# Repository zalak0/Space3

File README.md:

# Space3
Satellite code simulation and STM32 implementation of that code

## Structure

- **Simulation** folder includes code that simulates given code that is NOT in STM32.
- **STM32 Implementation** folder includes code that will be used for the STM32/in the satellite
> Organise each sub-folder into subsystem based folders rather than simulation-specific folders for modularity.

## STM32 tutorials
The following tutorials might help for STM32 coding. It might be a good idea to spend some time to actually learnt his since **STM32 is a complicated yet powerful platform**:

### STM32 basics

### Learn how to use HAL and functionality

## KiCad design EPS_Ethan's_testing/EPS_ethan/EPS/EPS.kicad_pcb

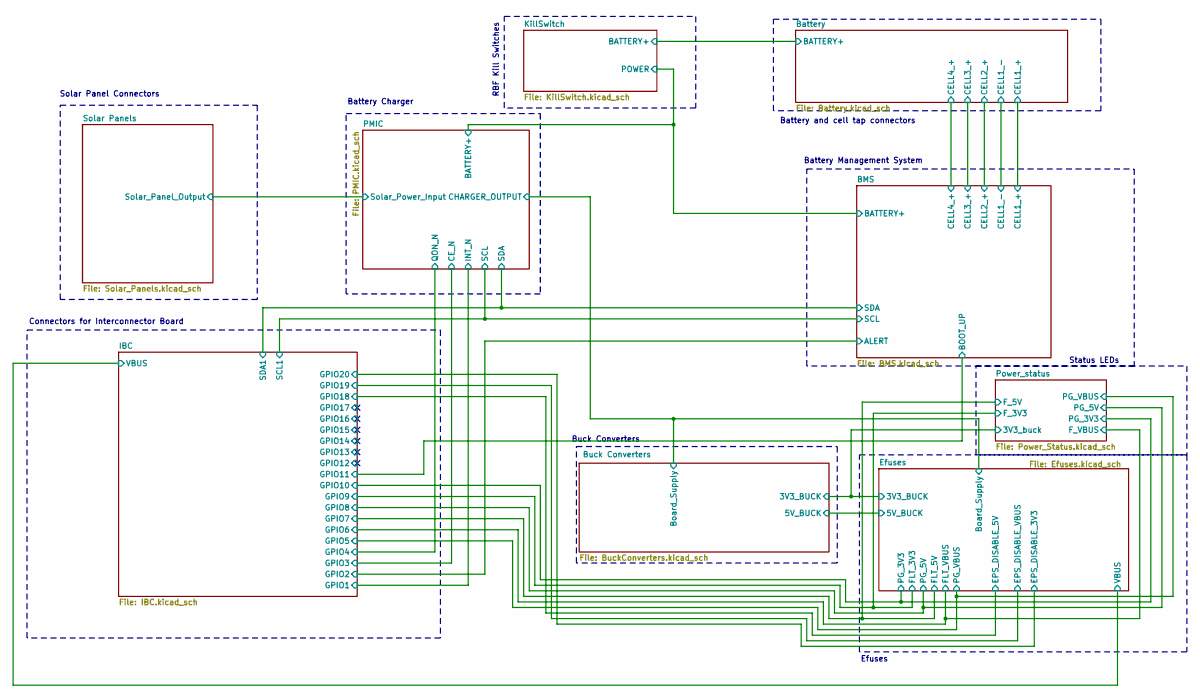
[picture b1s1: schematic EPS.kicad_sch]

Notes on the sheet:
Buck Converters
Battery Management System
Efuses
Battery and cell tap connectors
Status LEDs
Battery Charger
Connectors for Interconnector Board
Solar Panel Connectors
RBF Kill Switches

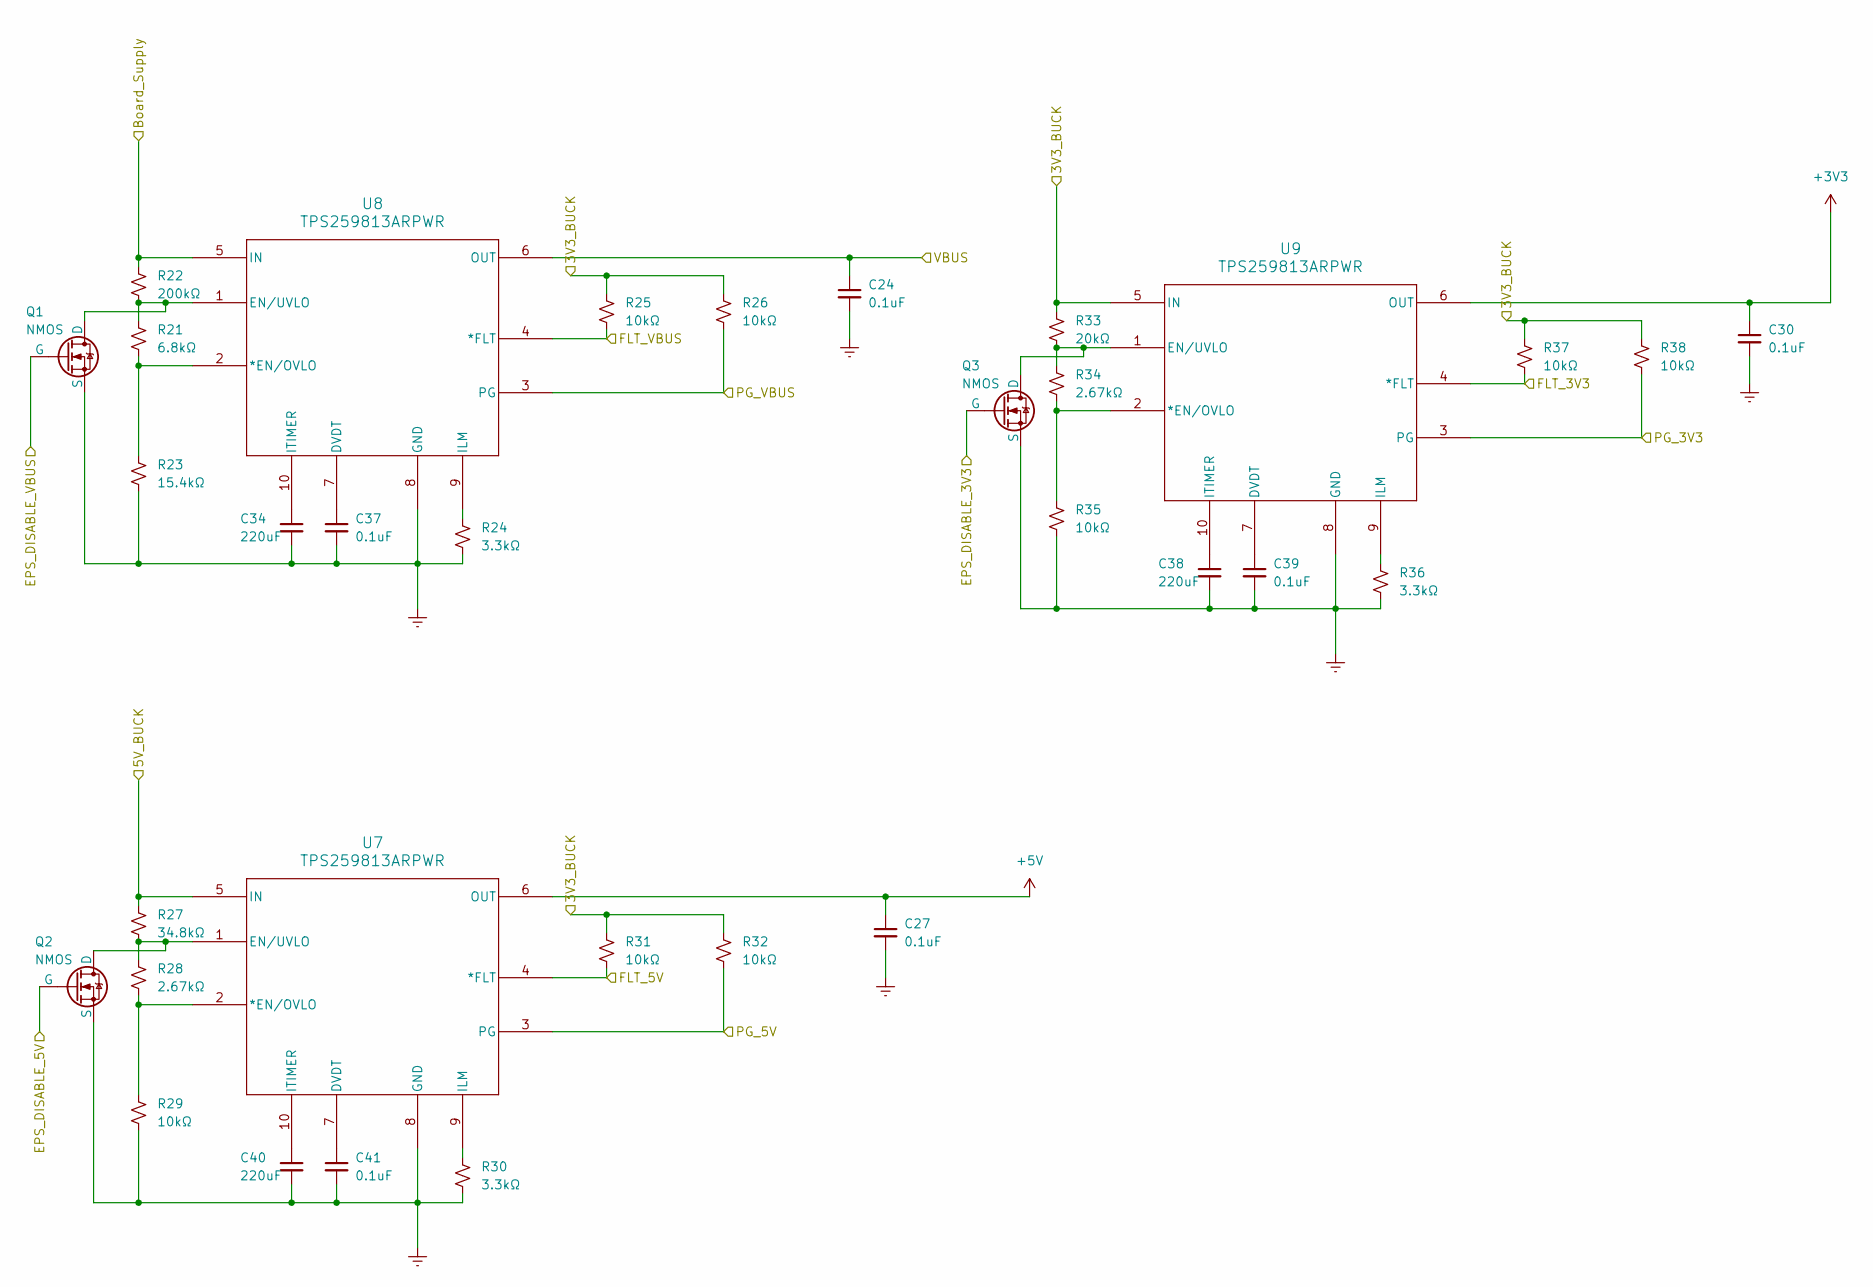
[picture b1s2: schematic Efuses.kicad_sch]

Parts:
C24, C27, C30, C37, C39, C41: 0.1uF; C_0402_1005Metric_Pad0.74x0.62mm_HandSolder; LCSC C1525
C34, C38, C40: 220uF; C_0402_1005Metric_Pad0.74x0.62mm_HandSolder; LCSC C16651
Q1, Q2, Q3: NMOS; SOT95P240X111-3N; LCSC C8545
R21: 6.8kΩ; R_0201_0603Metric; LCSC C144024
R22: 200kΩ; R_0201_0603Metric; LCSC C102705
R23: 15.4kΩ; R_0201_0603Metric; LCSC C166345
R24, R30, R36: 3.3kΩ; R_0201_0603Metric; LCSC C170206
R25, R26, R29, R31, R32, R35, R37, R38: 10kΩ; R_0201_0603Metric; LCSC C100126
R27: 34.8kΩ; R_0201_0603Metric; LCSC C180320
R28, R34: 2.67kΩ; R_0201_0603Metric; LCSC C158664
R33: 20kΩ; R_0201_0603Metric; LCSC C100134
U7, U8, U9: TPS259813ARPWR; VQFN10_RPW_TEX; LCSC C22427533

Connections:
+3V3: C30.1, U9.6 (OUT); also elsewhere on the board
+5V: C27.1, U7.6 (OUT); also elsewhere on the board
/Buck Converters/3V3_BUCK: R25.1, R26.1, R31.1, R32.1, R33.1, R37.1, R38.1, U9.5 (IN); also elsewhere on the board
/Buck Converters/5V_BUCK: R27.1, U7.5 (IN); also elsewhere on the board
/Buck Converters/Board_Supply: R22.1, U8.5 (IN); also elsewhere on the board
/Efuses/EPS_DISABLE_3V3: Q3.2 (G); also elsewhere on the board
/Efuses/EPS_DISABLE_5V: Q2.2 (G); also elsewhere on the board
/Efuses/EPS_DISABLE_VBUS: Q1.2 (G); also elsewhere on the board
/Efuses/FLT_3V3: R37.2, U9.4 (*FLT); also elsewhere on the board
/Efuses/FLT_5V: R31.2, U7.4 (*FLT); also elsewhere on the board
/Efuses/FLT_VBUS: R25.2, U8.4 (*FLT); also elsewhere on the board
/Efuses/PG_3V3: R38.2, U9.3 (PG); also elsewhere on the board
/Efuses/PG_5V: R32.2, U7.3 (PG); also elsewhere on the board
/Efuses/PG_VBUS: R26.2, U8.3 (PG); also elsewhere on the board
/Efuses/VBUS: C24.1, U8.6 (OUT); also elsewhere on the board
Earth: C24.2, C27.2, C30.2, C34.2, C37.2, C38.2, C39.2, C40.2, C41.2, Q1.3 (S), Q2.3 (S), Q3.3 (S), R23.2, R24.2, R29.2, R30.2, R35.2, R36.2, U7.8 (GND), U8.8 (GND), U9.8 (GND); also elsewhere on the board
unnamed: Q1.1 (D), R21.1, R22.2, U8.1 (EN/UVLO)
unnamed: Q2.1 (D), R27.2, R28.1, U7.1 (EN/UVLO)
unnamed: Q3.1 (D), R33.2, R34.1, U9.1 (EN/UVLO)
unnamed: R28.2, R29.1, U7.2 (*EN/OVLO)
unnamed: C41.1, U7.7 (DVDT)
unnamed: R30.1, U7.9 (ILM)
unnamed: C40.1, U7.10 (ITIMER)
unnamed: R21.2, R23.1, U8.2 (*EN/OVLO)
unnamed: C37.1, U8.7 (DVDT)
unnamed: R24.1, U8.9 (ILM)
unnamed: C34.1, U8.10 (ITIMER)
unnamed: R34.2, R35.1, U9.2 (*EN/OVLO)
unnamed: C39.1, U9.7 (DVDT)
unnamed: R36.1, U9.9 (ILM)
unnamed: C38.1, U9.10 (ITIMER)

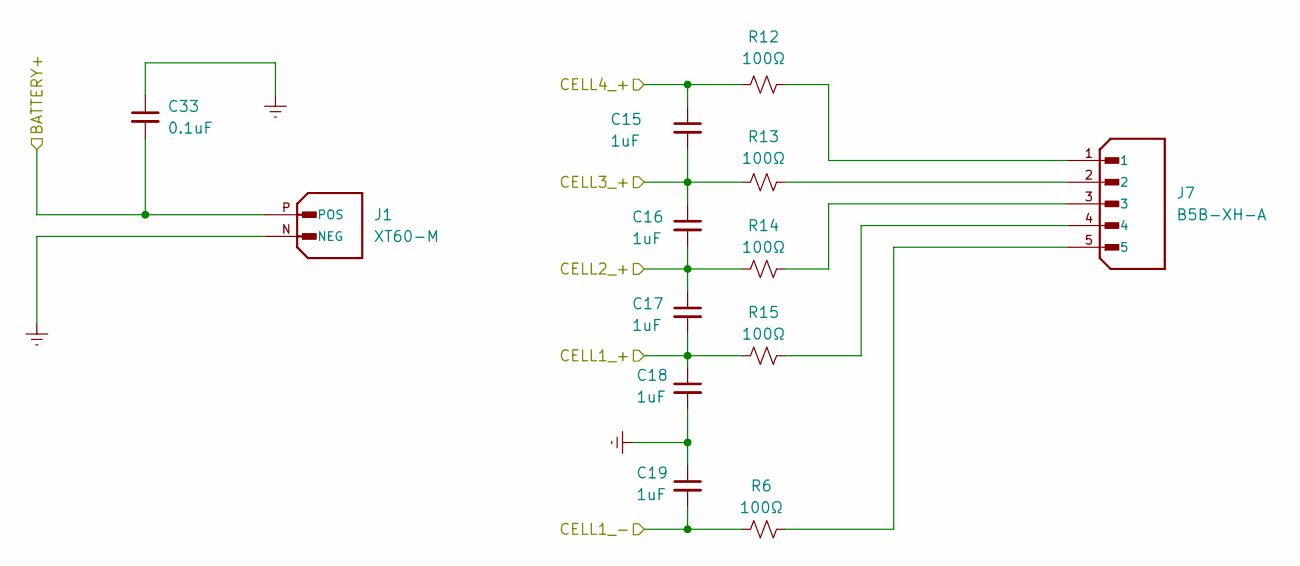
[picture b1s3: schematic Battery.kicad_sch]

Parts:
C15, C16, C17, C18, C19: 1uF; C_0402_1005Metric_Pad0.74x0.62mm_HandSolder; LCSC C14445
C33: 0.1uF; C_0402_1005Metric_Pad0.74x0.62mm_HandSolder; LCSC C1525
J1: XT60-M; AMASS_XT60-M; PARTREV V1.2; LCSC C98733
J7: B5B-XH-A; JST_B5B-XH-A; PARTREV 7/4/21; LCSC C157991
R6, R12, R13, R14, R15: 100Ω; R_0201_0603Metric; LCSC C77623

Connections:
/BMS/CELL1_+: C17.2, C18.1, R15.1; also elsewhere on the board
/BMS/CELL1_-: C19.2, R6.1; also elsewhere on the board
/BMS/CELL2_+: C16.2, C17.1, R14.1; also elsewhere on the board
/BMS/CELL3_+: C15.2, C16.1, R13.1; also elsewhere on the board
/BMS/CELL4_+: C15.1, R12.1; also elsewhere on the board
/Battery/BATTERY+: C33.2, J1.P (POS); also elsewhere on the board
Earth: C18.2, C19.1, C33.1, J1.N (NEG); also elsewhere on the board
unnamed: J7.1, R12.2
unnamed: J7.2, R13.2
unnamed: J7.3, R14.2
unnamed: J7.4, R15.2
unnamed: J7.5, R6.2

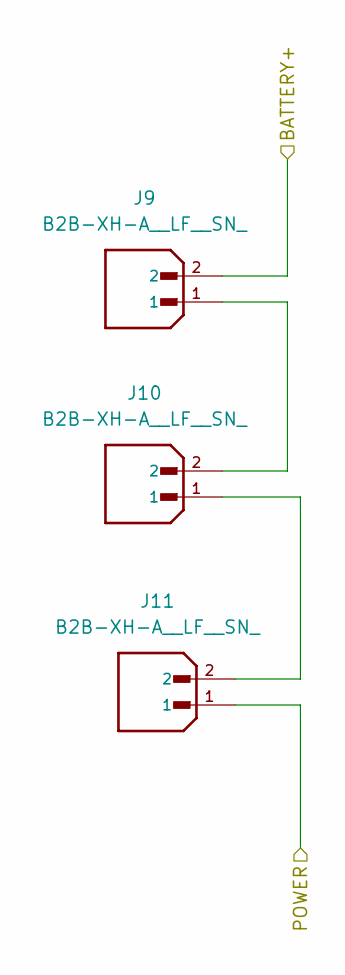
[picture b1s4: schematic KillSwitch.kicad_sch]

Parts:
J9, J10, J11: B2B-XH-A__LF__SN_; JST_B2B-XH-A__LF__SN_; PARTREV N/A; LCSC C158012

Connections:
/BMS/BATTERY+: J11.1; also elsewhere on the board
/Battery/BATTERY+: J9.2; also elsewhere on the board
unnamed: J10.1, J11.2
unnamed: J9.1, J10.2

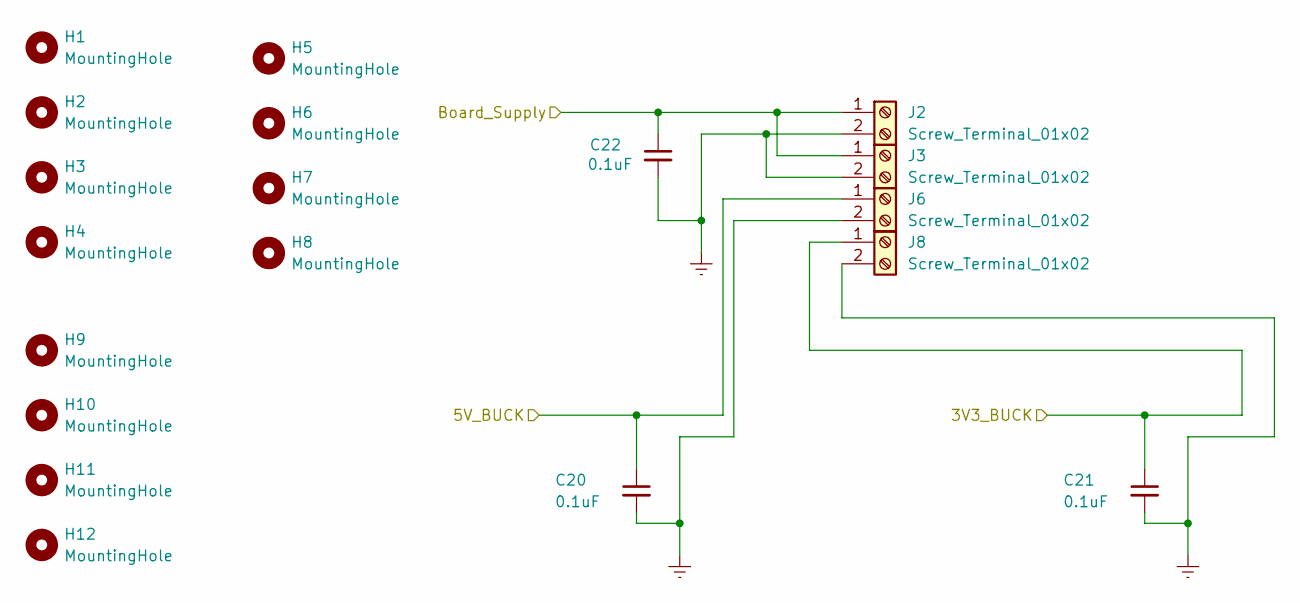
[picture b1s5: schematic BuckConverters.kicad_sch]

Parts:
C20, C21, C22: 0.1uF; C_0402_1005Metric_Pad0.74x0.62mm_HandSolder; LCSC C1525
H1, H2, H3, H4, H5, H6, H7, H8, H9, H10, H11, H12: MountingHole; MountingHole_3.2mm_M3
J2, J3, J6, J8: Screw_Terminal_01x02; HANDSON_KF301-2P; LCSC C474881

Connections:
/Buck Converters/3V3_BUCK: C21.1, J8.1; also elsewhere on the board
/Buck Converters/5V_BUCK: C20.1, J6.1; also elsewhere on the board
/Buck Converters/Board_Supply: C22.1, J2.1, J3.1; also elsewhere on the board
Earth: C20.2, C21.2, C22.2, J2.2, J3.2, J6.2, J8.2; also elsewhere on the board

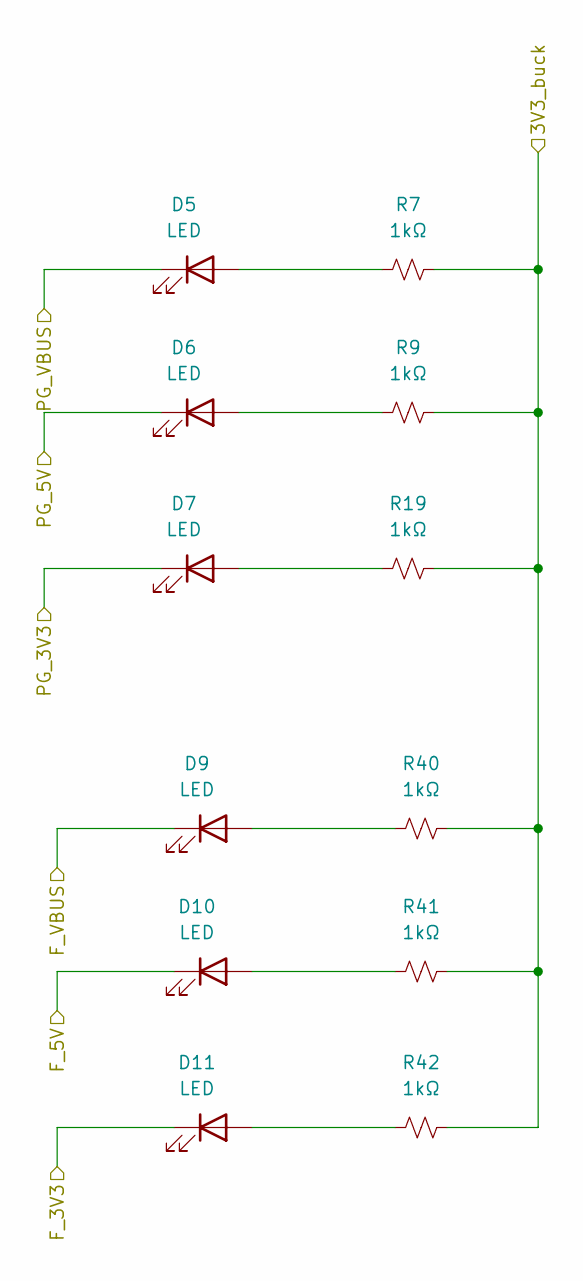
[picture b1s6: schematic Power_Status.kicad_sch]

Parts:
D5, D6, D7: LED; LED_0603_1608Metric; LCSC C510029
D9, D10, D11: LED; LED_0603_1608Metric; LCSC C79636
R7, R9, R19, R40, R41, R42: 1kΩ; R_0201_0603Metric; LCSC C100125

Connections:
/Buck Converters/3V3_BUCK: R7.2, R9.2, R19.2, R40.2, R41.2, R42.2; also elsewhere on the board
/Efuses/FLT_3V3: D11.1 (K); also elsewhere on the board
/Efuses/FLT_5V: D10.1 (K); also elsewhere on the board
/Efuses/FLT_VBUS: D9.1 (K); also elsewhere on the board
/Efuses/PG_3V3: D7.1 (K); also elsewhere on the board
/Efuses/PG_5V: D6.1 (K); also elsewhere on the board
/Efuses/PG_VBUS: D5.1 (K); also elsewhere on the board
unnamed: D5.2 (A), R7.1
unnamed: D6.2 (A), R9.1
unnamed: D7.2 (A), R19.1
unnamed: D9.2 (A), R40.1
unnamed: D10.2 (A), R41.1
unnamed: D11.2 (A), R42.1

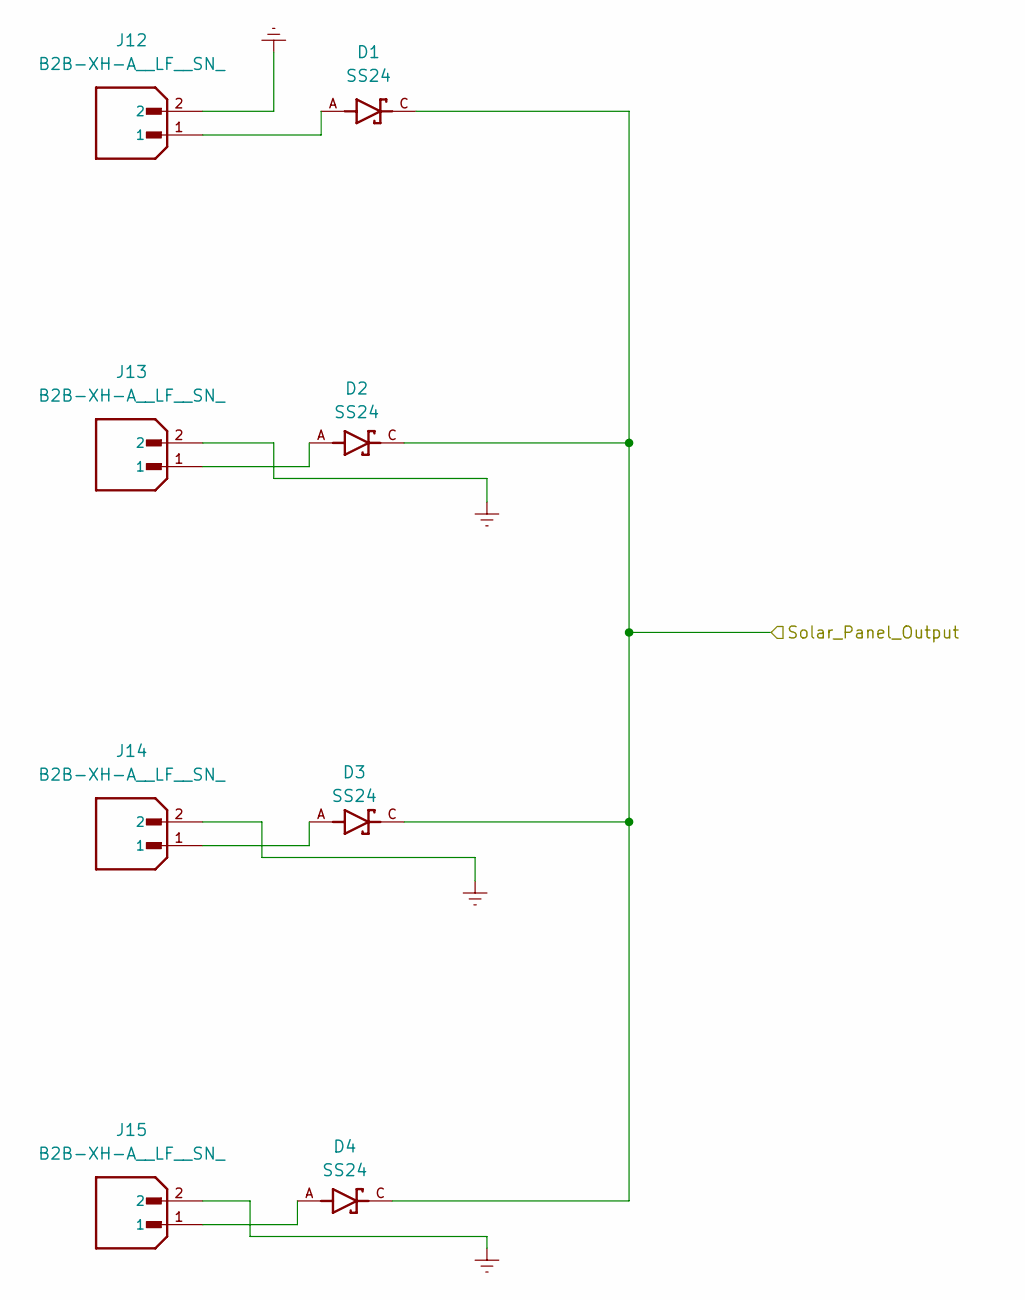
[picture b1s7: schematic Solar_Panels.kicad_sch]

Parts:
D1, D2, D3, D4: SS24; DIOM5336X265N; PARTREV 1.1.2; LCSC C50645
J12, J13, J14, J15: B2B-XH-A__LF__SN_; JST_B2B-XH-A__LF__SN_; PARTREV N/A; LCSC C158012

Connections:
/PMIC/Solar_Power_Input: D1.C, D2.C, D3.C, D4.C; also elsewhere on the board
Earth: J12.2, J13.2, J14.2, J15.2; also elsewhere on the board
unnamed: D1.A, J12.1
unnamed: D2.A, J13.1
unnamed: D3.A, J14.1
unnamed: D4.A, J15.1

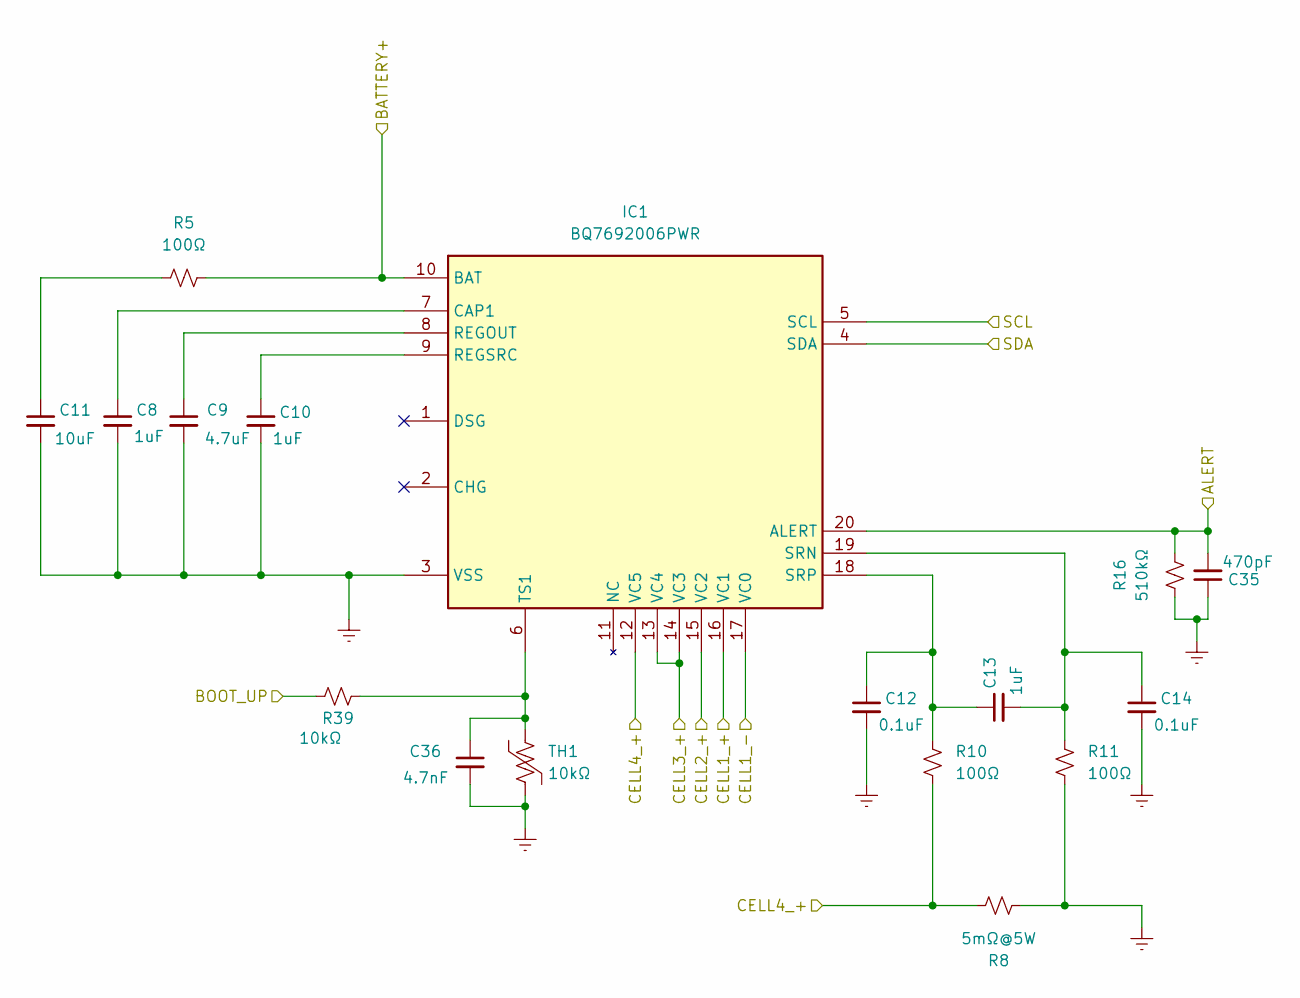
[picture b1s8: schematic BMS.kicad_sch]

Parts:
C8, C10, C13: 1uF; C_0402_1005Metric_Pad0.74x0.62mm_HandSolder; LCSC C83063
C9: 4.7uF; C_0402_1005Metric_Pad0.74x0.62mm_HandSolder; LCSC C23687
C11: 10uF; C_0402_1005Metric_Pad0.74x0.62mm_HandSolder; LCSC C77000
C12, C14: 0.1uF; C_0402_1005Metric_Pad0.74x0.62mm_HandSolder; LCSC C1525
C35: 470pF; C_0402_1005Metric_Pad0.74x0.62mm_HandSolder; LCSC C1537
C36: 4.7nF; C_0402_1005Metric_Pad0.74x0.62mm_HandSolder; LCSC C1538
IC1: BQ7692006PWR; SOP65P640X120-20N; Mouser Part Number 595-BQ7692006PWR
R5, R10, R11: 100Ω; R_0201_0603Metric; LCSC C77623
R8: 5mΩ@5W; RESC6432X90N; LCSC C840612
R16: 510kΩ; R_0201_0603Metric; LCSC C295805
R39: 10kΩ; R_0201_0603Metric; LCSC C100126
TH1: 10kΩ; R_0201_0603Metric; LCSC C92037

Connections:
/BMS/ALERT: C35.2, IC1.20 (ALERT), R16.2; also elsewhere on the board
/BMS/BATTERY+: IC1.10 (BAT), R5.1; also elsewhere on the board
/BMS/BOOT_UP: R39.1; also elsewhere on the board
/BMS/CELL1_+: IC1.16 (VC1); also elsewhere on the board
/BMS/CELL1_-: IC1.17 (VC0); also elsewhere on the board
/BMS/CELL2_+: IC1.15 (VC2); also elsewhere on the board
/BMS/CELL3_+: IC1.13 (VC4), IC1.14 (VC3); also elsewhere on the board
/BMS/CELL4_+: IC1.12 (VC5), R8.1, R10.2; also elsewhere on the board
/BMS/SCL: IC1.5 (SCL); also elsewhere on the board
/BMS/SDA: IC1.4 (SDA); also elsewhere on the board
Earth: C8.2, C9.2, C10.2, C11.2, C12.2, C14.2, C35.1, C36.2, IC1.3 (VSS), R8.2, R11.2, R16.1, TH1.2; also elsewhere on the board
unnamed: C11.1, R5.2
unnamed: C8.1, IC1.7 (CAP1)
unnamed: C9.1, IC1.8 (REGOUT)
unnamed: C10.1, IC1.9 (REGSRC)
unnamed: C13.2, C14.1, IC1.19 (SRN), R11.1
unnamed: C12.1, C13.1, IC1.18 (SRP), R10.1
unnamed: C36.1, IC1.6 (TS1), R39.2, TH1.1

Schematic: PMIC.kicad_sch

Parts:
C1, C25: 0.1uF; C_0402_1005Metric_Pad0.74x0.62mm_HandSolder; LCSC C1525
C2, C3: 47nF; C_0402_1005Metric_Pad0.74x0.62mm_HandSolder; LCSC C77012
C4: 4.7uF; C_0402_1005Metric_Pad0.74x0.62mm_HandSolder; LCSC C23687
C5: 0.1uF; C_0402_1005Metric_Pad0.74x0.62mm_HandSolder; LCSC C77000
C6, C7, C23, C26, C28, C29, C31, C32: 10uF; C_0402_1005Metric_Pad0.74x0.62mm_HandSolder; LCSC C77000
D8: LED; LED_0603_1608Metric; LCSC C510029
L1: 1.0uH; IND_ETQP3M1R0KVP; LCSC C409620
R1: 27kΩ; R_0201_0603Metric; LCSC C273283
R2: 13kΩ; R_0201_0603Metric; LCSC C158813
R3: 100Ω; R_0201_0603Metric; LCSC C77623
R4: 30kΩ; R_0201_0603Metric; LCSC C138105
R17, R20, R43: 10kΩ; R_0201_0603Metric; LCSC C100126
R18: 6.04kΩ; R_0201_0603Metric; LCSC C158428
TH2: 10KΩ; R_0201_0603Metric; LCSC C92037
U5: BQ25798RQMR; RQM0029A-MFG_fixed; LCSC C2876593

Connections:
+3V3: R17.1, R43.1; also elsewhere on the board
/BMS/BATTERY+: R3.2, U5.22 (BAT), U5.23 (BAT), U5.24 (SDRV); also elsewhere on the board
/BMS/SCL: U5.14 (SCL); also elsewhere on the board
/BMS/SDA: U5.15 (SDA); also elsewhere on the board
/Buck Converters/Board_Supply: C25.1, C26.1, C28.1, C29.1, C31.1, C32.1, U5.25 (SYS); also elsewhere on the board
/IBC/GPIO1: R43.2, U5.21 (INT_N); also elsewhere on the board
/IBC/GPIO3: R17.2, U5.13 (CE_N); also elsewhere on the board
/IBC/GPIO4: U5.12 (QON_N); also elsewhere on the board
/PMIC/REGEN: C4.1, R2.1, R18.1, U5.5 (REGN)
/PMIC/Solar_Power_Input: C1.1, U5.2 (VBUS), U5.3 (VBUS); also elsewhere on the board
Earth: C1.2, C4.2, C5.2, C6.2, C7.2, C23.2, C25.2, C26.2, C28.2, C29.2, C31.2, C32.2, R1.2, R4.1, R20.2, TH2.2, U5.10 (ACDRV2), U5.11 (ACDRV1), U5.27 (GND); also elsewhere on the board
unnamed: D8.2 (A), R18.2
unnamed: D8.1 (K), U5.1 (STAT)
unnamed: R3.1, U5.18 (BATP)
unnamed: C2.1, U5.4 (BTST1)
unnamed: C3.2, U5.19 (BTST2)
unnamed: R2.2, R20.1, U5.17 (ILIM_HIZ)
unnamed: C5.1, C6.1, C7.1, C23.1, U5.29 (PMID)
unnamed: R1.1, U5.20 (PROG)
unnamed: C2.2, L1.2, U5.28 (SW1)
unnamed: C3.1, L1.1, U5.26 (SW2)
unnamed: R4.2, TH2.1, U5.16 (TS)
unnamed: U5.8 (VAC2), U5.9 (VAC1)

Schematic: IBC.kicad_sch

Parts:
J4, J5: M20-6112045; HARWIN_M20-6112045; PARTREV 13

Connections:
+3V3: J4.3; also elsewhere on the board
+5V: J4.2; also elsewhere on the board
/BMS/ALERT: J4.9; also elsewhere on the board
/BMS/BOOT_UP: J4.27; also elsewhere on the board
/BMS/SCL: J4.6; also elsewhere on the board
/BMS/SDA: J4.8; also elsewhere on the board
/Efuses/EPS_DISABLE_3V3: J4.10; also elsewhere on the board
/Efuses/EPS_DISABLE_5V: J4.14; also elsewhere on the board
/Efuses/EPS_DISABLE_VBUS: J4.12; also elsewhere on the board
/Efuses/FLT_3V3: J4.23; also elsewhere on the board
/Efuses/FLT_5V: J4.19; also elsewhere on the board
/Efuses/FLT_VBUS: J4.17; also elsewhere on the board
/Efuses/PG_3V3: J4.25; also elsewhere on the board
/Efuses/PG_5V: J4.21; also elsewhere on the board
/Efuses/PG_VBUS: J4.15; also elsewhere on the board
/Efuses/VBUS: J4.1; also elsewhere on the board
/IBC/GPIO1: J4.7; also elsewhere on the board
/IBC/GPIO3: J4.11; also elsewhere on the board
/IBC/GPIO4: J4.13; also elsewhere on the board
/IBC/GPIO12: J4.29
/IBC/GPIO13: J4.31
/IBC/GPIO14: J4.33
/IBC/GPIO15: J4.35
/IBC/GPIO16: J4.37
/IBC/GPIO17: J4.39
Earth: J4.4, J4.5; also elsewhere on the board

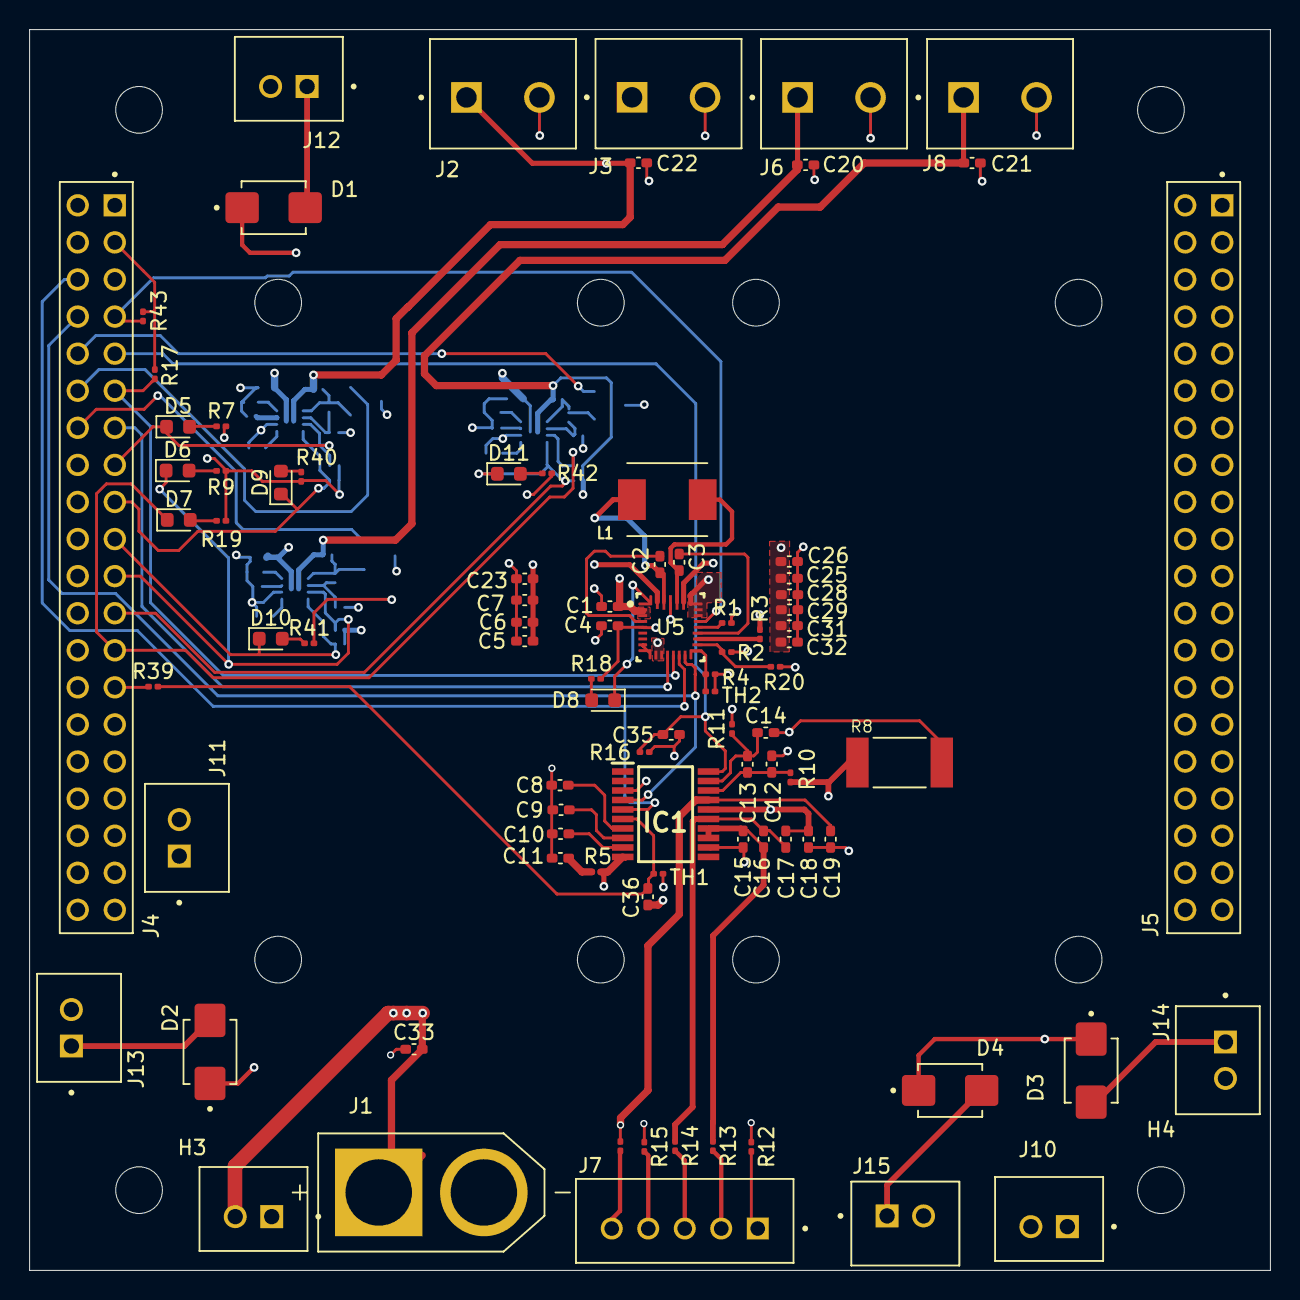
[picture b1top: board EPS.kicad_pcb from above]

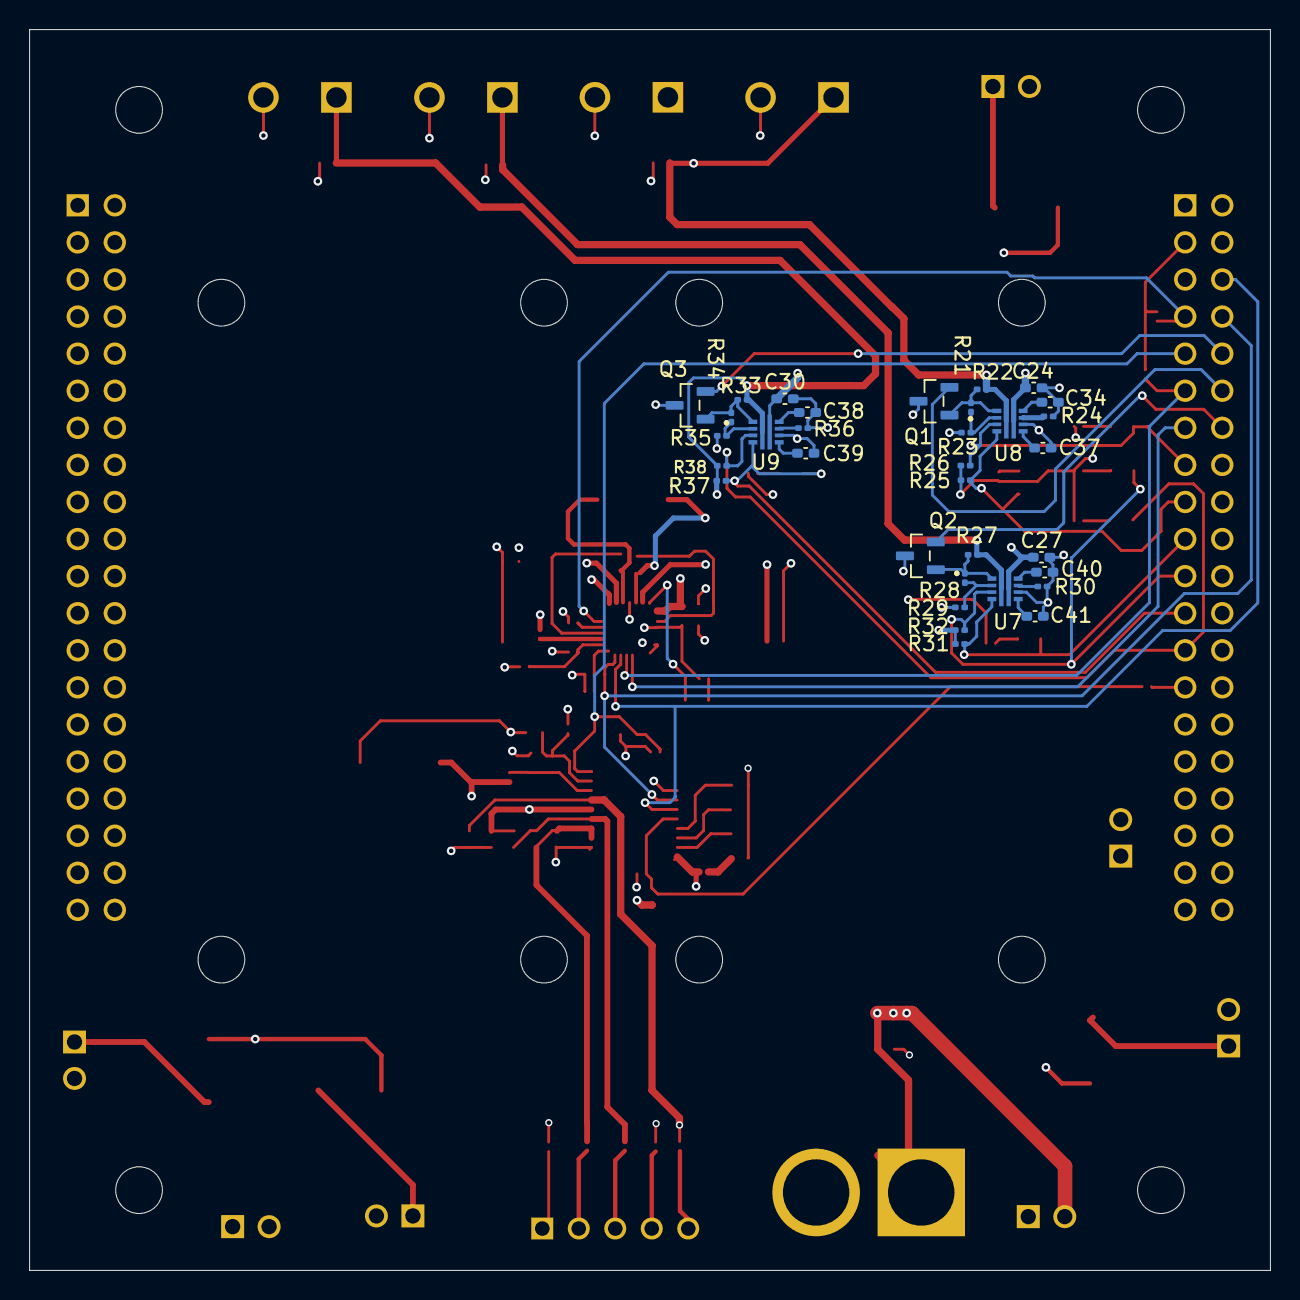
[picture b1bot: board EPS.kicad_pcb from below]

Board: 4 copper layers, 85.0 x 85.0 mm, 133 parts (33 on the bottom side), 83 nets.

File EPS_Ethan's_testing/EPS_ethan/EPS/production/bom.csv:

Designator,Footprint,Quantity,Value,LCSC Part #
"C1, C25",0402,2,0.1uF, C1525
"C10, C13, C8",0402,3,1uF,C83063
C11,0402,1,10uF,C77000 
"C12, C14",0402,2,0.1uF,C1525 
"C15, C16, C17, C18, C19",0402,5,1uF,C14445
"C2, C3",0402,2,47nF,C77012
"C20, C21, C22, C24, C27, C30, C33, C37, C39, C41",0402,10,0.1uF,C1525
"C23, C26, C28, C29, C31, C32, C6, C7",0402,8,10uF,C77000
"C34, C38, C40",0402,3,220uF,C16651
C35,0402,1,470pF,C1537
C36,0402,1,4.7nF,C1538
C4,0402,1,4.7uF,C23687
C5,0402,1,0.1uF,C77000
C9,0402,1,4.7uF,C23687 
"D1, D2, D3, D4",DIOM5336X265N,4,SS24,C50645
"D10, D11, D9",0603,3,LED,C79636
"D5, D6, D7, D8",0603,4,LED,C510029
IC1,SOP65P640X120-20N,1,BQ7692006PWR,C181647
J1,AMASS_XT60-M,1,XT60-M, C98733
"J10, J11, J12, J13, J14, J15, J9",JST_B2B-XH-A__LF__SN_,7,B2B-XH-A__LF__SN_,C158012
"J2, J3, J6, J8",HANDSON_KF301-2P,4,Screw_Terminal_01x02,C474881
"J4, J5",HARWIN_M20-6112045,2,M20-6112045,
J7,JST_B5B-XH-A,1,B5B-XH-A,C157991
L1,IND_ETQP3M1R0KVP,1,1.0uH,C409620
"Q1, Q2, Q3",SOT95P240X111-3N,3,NMOS,C8545
R1,0201,1,27kΩ,C273283
"R10, R11, R12, R13, R14, R15, R3, R5, R6",0201,9,100Ω,C77623
R16,0201,1,510kΩ,C295805
"R17, R20, R25, R26, R29, R31, R32, R35, R37, R38, R39, R43",0201,12,10kΩ,C100126
R18,0201,1,6.04kΩ,C158428
"R19, R40, R41, R42, R7, R9",0201,6,1kΩ,C100125
R2,0201,1,13kΩ,C158813
R21,0201,1,6.8kΩ,C144024
R22,0201,1,200kΩ,C102705
R23,0201,1,15.4kΩ,C166345
"R24, R30, R36",0201,3,3.3kΩ,C170206
R27,0201,1,34.8kΩ,C180320
"R28, R34",0201,2,2.67kΩ,C158664
R33,0201,1,20kΩ,C100134
R4,0201,1,30kΩ,C138105
R8,RESC6432X90N,1,5mΩ@5W,C840612
"TH1, TH2",0201,2,10kΩ,C92037
U5,RQM0029A-MFG_fixed,1,BQ25798RQMR,C2876593
"U7, U8, U9",VQFN10_RPW_TEX,3,TPS259813ARPWR,C22427533

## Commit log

2026-05-13 Implementing ACS simulation files and basic structure
2026-05-13 Enhance README with structure and tutorial links
    Added structure and STM32 tutorials sections to README.
2026-05-13 Replace video tags with thumbnail links
    Updated video links to use thumbnail images for better presentation.
2026-05-17 Uploaded Controller and External Disturbances code and results
2026-05-17 Removed unnecessary figures and data entries
2026-06-05 High-level integration implementation of code
2026-06-07 ADS AIT Code push
2026-06-07 EPS code Push
2026-06-07 Payload code push
2026-06-07 Added STM32 testing files used for OBC and ADCS
2026-06-07 Added updated working ACS simulation code
2026-06-07 Removed unecessary ACS files and clarity
2026-06-08 payload_stm_langmuir_probe test run
2026-06-08 Update payload code
    - Reads 1 Langmuir
    - Also gives i2c error message
2026-06-08 Update Payload code
    - Reads 2 Langmuir now!!!
    - Also gives i2c (external) error status
2026-06-09 old gps code as emergency
2026-06-09 ESP shows nmea messages
    - Code on STM sends NMEA messages
    - Code on ESP reads NMEA messages
    (but no parsing yet)
2026-06-09 STM parses GPS messages
    - STM can read GPS messages and parse Lat, Long, no fix
    - ESP displays when there is no fix
2026-06-09 Payload - Activates burn wire
    - A bit dodgy, but might just be the connection
2026-06-09 Payload - Discovery Board testing
    - Did not work, but just to store it on github anyway
2026-06-09 Payload - Store I-V values
    - Not tested yet
2026-06-09 Payload - Modify configurations
    It kept complaining about having floats
2026-06-10 Payload - Update pins to match actual pins
    - UNTESTED
2026-06-10 Payload - Made Langmuir code which matches pins
    - NOT TESTED ON OBC YET
2026-06-10 Payload - Update Burn wire code to match pins
    - NOT TESTED ON OBC YET
2026-06-10 Payload - Made combined code which does Langmuir and GPS
    - NOT TESTED ON OBC YET
2026-06-10 Payload - Included burn wire into combined code just in case
    - NOT TESTED YET ON OBC
    - Also created Combined_Test which is just a backup
2026-06-11 Added the testing code for EPS
    Just import all of the src and include codes, and run the main. You will need to connect to UART via UART to USB or connect to another ESP32 or arduino
    Also set up ioc well
2026-06-11 Payload - Burn wire code works on STM
    - Burn wire actual tested
2026-06-11 UART READER
2026-06-11 EPS telem
2026-06-11 Payload - Fixed langmuir code
    - Includes gpio pin for activating
2026-06-11 Payload - Combined code has corrected langmuir and gps
    - Also includes burn wire for checking
2026-06-11 Payload - Combined actual file works
    - This works
    - Not cleaned yet
2026-06-11 Payload - Combined_Actual_Clean works!
    - Tested, behaviour as expected
2026-06-11 Fully integrated EPS code for comms
2026-06-11 Working simulation of Bdot and APLQR
2026-06-11 Payload - Combined actual clean has struct now
2026-06-11 Updated Space integration code
2026-06-12 Full ADS code push
2026-06-12 ADS - create .project file
    - so we can all open it
2026-06-12 COMMS integration
2026-06-12 Added functions to change in any state
2026-06-12 ADS - test code to just read imu
2026-06-12 Functional compiled integrated GOOSE code
2026-06-12 Working comms but no memory writing
2026-06-12 Initialise langmuir and gps
2026-06-12 Initialise gps correctly
2026-06-12 Final ADS push. Godspeed
2026-06-12 Print instead of store
